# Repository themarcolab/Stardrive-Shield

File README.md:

# STARDRIVE SHIELD

## Introduction
This project has been born because I have been trying to develop an ESC (hardware and firmware) on my own. 
While the most challenging part has been the firmware (being myself a hardware guy), the most frustrating part has been not finding a flexible hardware platform to develop upon.

So I designed one: **STARDRIVE SHIELD**

## Description 
This is a project with the goal of creating a NUCLEO-64 compatible shield to be used as a flexible platform to develop and test ESC firmware, but also for educational purposes. To do so, I included as many features as possible. These features are not mandatory, but they can be implemented (or not) in the firmware (e.g. SPI, I2C, CAN, HALL) or configured through the hardware interface (e.g. overcurrent protection, 6 or 3 PWM). In this way, the STARDRIVE SHIELD grants flexibility to the developer and it is adapt to various needs.

## Features
The **STARDRIVE SHIELD** is built around the [STDRIVE101](https://www.st.com/en/power-management/stdrive101.html)  gate driver and implementing [BSZ099N06LS5](https://www.infineon.com/part/BSZ099N06LS5) MOSFETs.
It presents 3 in-line shunt resistors and 3 relative [INA240A2](https://www.ti.com/lit/ds/symlink/ina240.pdf?ts=1785176124311&ref_url=https%253A%252F%252Fwww.google.com%252F) current sense amplifiers.

With **STARDRIVE SHIELD** you can implement from 6 step to FOC motor control algorithms.

I designed it to be compatible with Nucleo-G474 and Nucleo-F446. Compatibility with other boards has to be verified. 

### Electrical Characteristics
+ Inprut Voltage V<sub>in</sub> = 12 - 48 V
+ Maximum DC current I<sub>dc,max</sub> = 20 A

### Hardware Characteristiscs
+ Three phase gate driver [STDRIVE101](https://www.st.com/en/power-management/stdrive101.html)
  + Configurable 3PWM or 6PWM through the DIP switch
  + Overcurrent protection can be enabled or disabled through the DIP switch.
  + V<sub>ds</sub> protection configurable with resistor divider (disabled by default)
+ [BSZ099N06LS5](https://www.infineon.com/part/BSZ099N06LS5) MOSFETs
+ 3 in-line shunt resistors (1mOhm) with relative 3 INA240A2 Current Sensors
+ JST connectors to implement:
  + I2C (e.g. for magnetic encoder such as [AS5046](https://mm.digikey.com/Volume0/opasdata/d220001/medias/docus/1138/AS5046.pdf))
  + SPI (e.g. for magnetic encoder such as [AS5047P](https://look.ams-osram.com/m/d05ee39221f9857/original/AS5047P-DS000324.pdf))
  + CAN
  + HALL sensors (some BLDC motors have embedded Hall sensors)
  + 3 NTC temperature sensors
+ 10k Potentiometer to use as throttle signal (or whatever you want)
+ 3 GPIO driven LEDs (1 Red, 1 Blue, 1 Green)
+ 1 FAULT LED (RED)
+ CAN RX and TX LEDs
+ Power Good LEDs

## Inspirations
For this project I took inspiration from the [VESC Project](https://vesc-project.com/) and [EVALSTDRIVE101](https://www.st.com/en/evaluation-tools/evalstdrive101.html#cad-resources)

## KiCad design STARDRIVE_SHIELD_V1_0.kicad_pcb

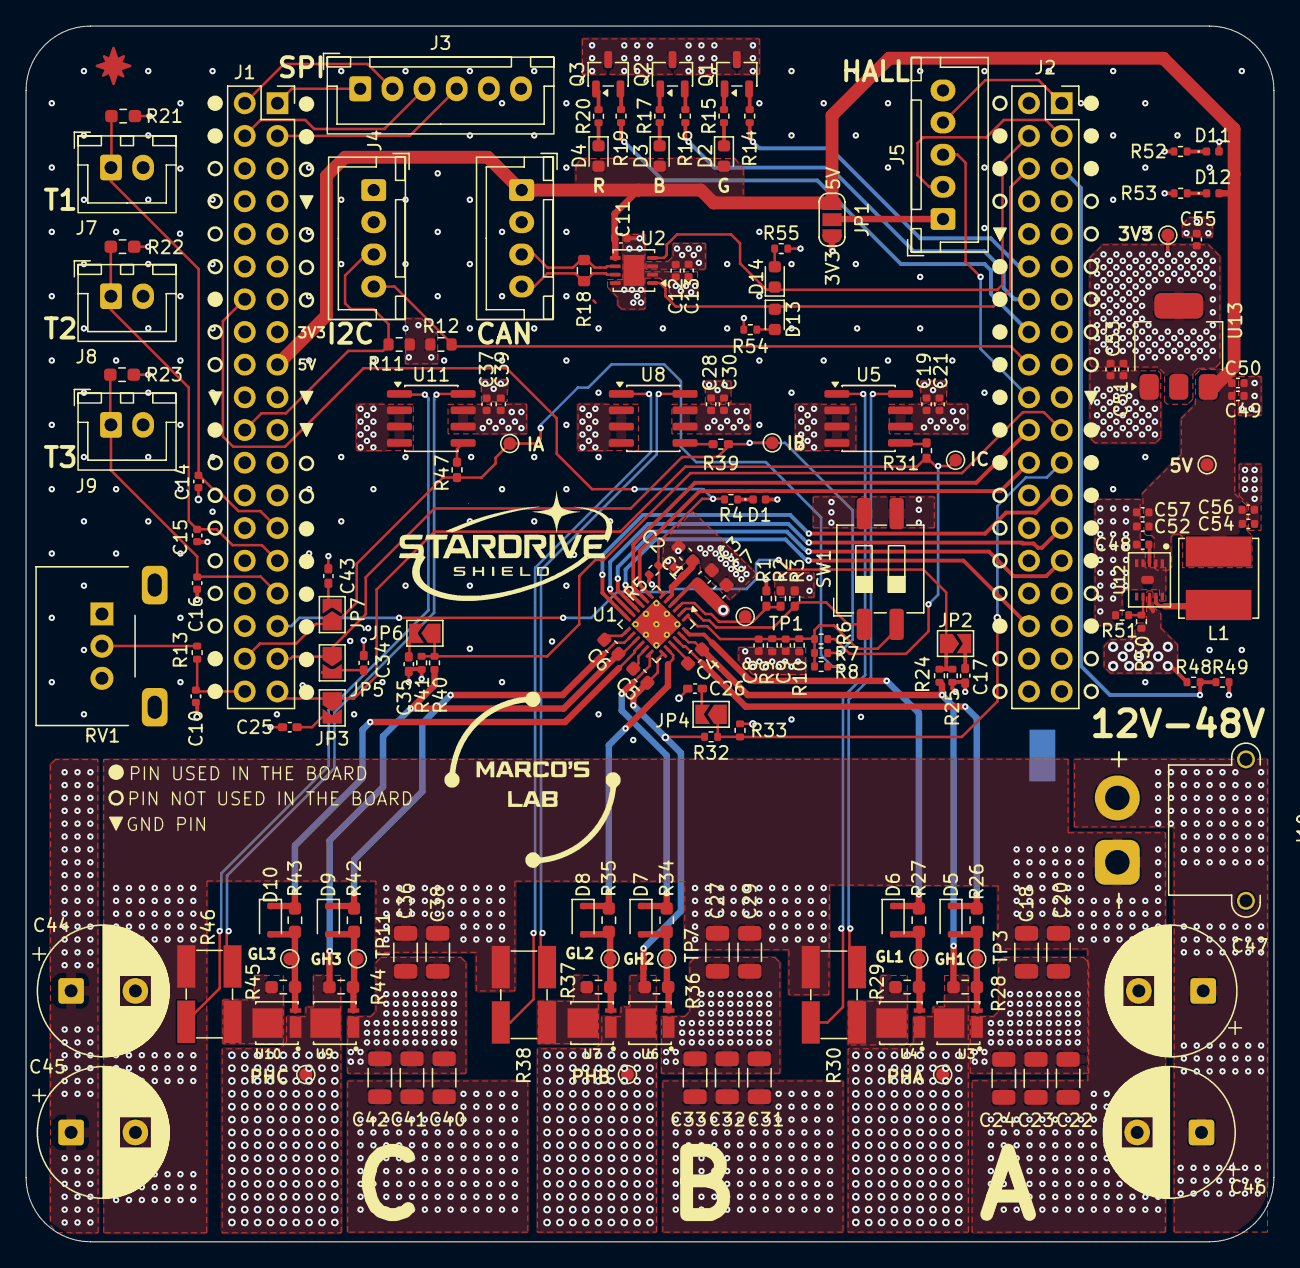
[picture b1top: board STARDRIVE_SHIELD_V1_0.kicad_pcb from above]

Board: 4 copper layers, 97.0 x 94.5 mm, 178 parts (1 on the bottom side), 98 nets.

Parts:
C1: 4u7 25V; C_0603_1608Metric
C2: 100n 25V; C_0402_1005Metric
C3: 100n 100V; C_0603_1608Metric
C4, C5, C6: 1u 25V; C_0603_1608Metric
C7: 1u 100V; C_0603_1608Metric
C8: 3n3 10V; C_0402_1005Metric
C9: NP; C_0402_1005Metric
C10, C13, C21, C30, C39, C50, C51, C52: 100n 10V; C_0402_1005Metric
C11, C12, C14, C15, C16, C19, C28, C37: 2u2 10V; C_0402_1005Metric
C17, C25, C26, C34, C35, C43: 100n 10V; C_0402_1005Metric_Pad0.74x0.62mm_HandSolder
C18, C20, C22, C23, C24, C27, C29, C31, C32, C33, C36, C38, C40, C41, C42: 4u7 100V; C_1206_3216Metric
C44, C45, C46, C47: 220u 63V; CP_Radial_D10.0mm_P5.00mm
C48: 470n 10V; C_0402_1005Metric
C49, C53, C54, C55, C56, C57: 10u 10V; C_0402_1005Metric
D1: RED; LED_0402_1005Metric
D2, D14: GREEN; LED_0603_1608Metric
D3: BLUE; LED_0603_1608Metric
D4, D13: RED; LED_0603_1608Metric
D5, D6, D7, D8, D9, D10: BAT43WS; D_SOD-323F
D11, D12: GREEN; LED_0402_1005Metric
J1, J2: Conn_02x19_Odd_Even; PinSocket_2x19_P2.54mm_Vertical
J3: Conn_01x06_Pin; JST_XH_B6B-XH-A_1x06_P2.50mm_Vertical
J4, J6: Conn_01x04_Pin; JST_XH_B4B-XH-A_1x04_P2.50mm_Vertical
J5: Conn_01x05_Pin; JST_XH_B5B-XH-A_1x05_P2.50mm_Vertical
J7, J8, J9: Conn_01x02_Pin; JST_XH_B2B-XH-A_1x02_P2.50mm_Vertical
J10: XT30PW-M; AMASS_XT30PW-M_1x02_P2.50mm_Horizontal
JP1: SolderJumper_3_Open; SolderJumper-3_P1.3mm_Open_RoundedPad1.0x1.5mm_NumberLabels
JP2, JP3, JP4, JP5, JP6, JP7: SolderJumper; SolderJumper-2_P1.3mm_Open_TrianglePad1.0x1.5mm
L1: 68u; L_Bourns_SRN6045TA
NT1: NetTie_2; NetTie-2_SMD_Pad2.0mm
Q1, Q2, Q3: NMOS; SOT-23-3
R1, R31, R39, R47: 0R; R_0402_1005Metric_Pad0.72x0.64mm_HandSolder
R2: NP; R_0402_1005Metric_Pad0.72x0.64mm_HandSolder
R3: 51k; R_0402_1005Metric_Pad0.72x0.64mm_HandSolder
R4: 470R; R_0402_1005Metric
R5, R6, R7, R8: 10k; R_0402_1005Metric
R9: 1k1; R_0402_1005Metric
R10: NP; R_0402_1005Metric
R11, R12: NP; R_0603_1608Metric
R13, R14, R16, R19: 100R; R_0402_1005Metric
R15, R17, R53, R54, R55: 360R; R_0402_1005Metric
R18: 120R; R_0603_1608Metric
R20: 620R; R_0402_1005Metric
R21, R22, R23, R28, R29, R36, R37, R44, R45: 10k; R_0603_1608Metric_Pad0.98x0.95mm_HandSolder
R24, R32, R40, R48: 56k; R_0402_1005Metric
R25, R33, R41, R49: 3k3; R_0402_1005Metric
R26, R27, R34, R35, R42, R43: 54R9; R_0603_1608Metric_Pad0.98x0.95mm_HandSolder
R30, R38, R46: 1mR; R_Shunt_Ohmite_LVK25
R50: 100k; R_0402_1005Metric
R51: 15k; R_0402_1005Metric
R52: 220R; R_0402_1005Metric
RV1: R_Potentiometer; Potentiometer_Alps_RK09L_Single_Horizontal
SW1: SW_DIP_x02; SW_DIP_SPSTx02_Slide_6.7x6.64mm_W8.61mm_P2.54mm_LowProfile
TP1, TP2, TP3, TP4, TP5, TP6, TP7, TP8, TP9, TP10, TP11, TP12, TP13, TP14, TP15: TestPoint; TestPoint_Pad_D1.0mm
U1: STDRIVE101; QFN-24-1EP_4x4mm_P0.5mm_EP2.8x2.8mm_ThermalVias
U2: TJA1051TK-3; HVSON-8-1EP_3x3mm_P0.65mm_EP1.6x2.4mm
U3, U4, U6, U7, U9, U10: BSZ099N06LS5; PG-TSDSON-8
U5, U8, U11: INA240A2D; SOIC-8_3.9x4.9mm_P1.27mm
U12: L7983; DFN-10-1EP_3mmX3mm_P0.5mm_ExposedPad_0.62x0.98mm
U13: LD1117S33TR; SOT-223-3_TabPin2

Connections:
+3V3: C12.1, C13.1, C19.1, C21.1, C28.1, C30.1, C37.1, C39.1, C51.1, C53.1, C55.1, J1.15, J3.6, J4.1, J7.2, J8.2, J9.2, R11.1, R12.1, RV1.1, U2.3 (VCC), U5.6 (V+), U5.7 (REF1), U8.6 (V+), U8.7 (REF1), U11.6 (V+), U11.7 (REF1), U13.2 (VO)
+5V: C11.1, C49.1, C50.1, C52.1, C54.1, C56.1, C57.1, D2.2 (A), D3.2 (A), D4.2 (A), D12.2 (A), J1.17, J6.1, JP1.3 (B), L1.2, TP15.1 (1_1), U2.5 (VIO), U12.1 (VOUT/FB), U12.2 (VBIAS), U13.3 (VI)
+12V: C1.1, C2.1, U1.5 (REG12)
/Connectors/ADC1.CURR1: J1.37, JP3.1 (A), R6.1, R31.1, TP5.1 (1_1)
/Connectors/ADC1.CURR2: J1.35, JP5.1 (A), R7.1, R39.1, TP9.1 (1_1)
/Connectors/ADC1.CURR3: J1.36, JP7.1 (A), R8.1, R47.1, TP13.1 (1_1)
/Connectors/ADC1.TEMP1: C14.1, J1.27, J7.1, R21.2
/Connectors/ADC1.TEMP2: C15.1, J1.29, J8.1, R22.2
/Connectors/ADC1.TEMP3: C16.1, J1.31, J9.1, R23.2
/Connectors/ADC1.THROTTLE: C10.1, J1.38, R13.1
/Connectors/ADC1.VOLTAGE1: J1.33, JP2.1 (A), R24.2, R25.1
/Connectors/ADC1.VOLTAGE2: J2.23, JP4.1 (A), R32.2, R33.1
/Connectors/ADC1.VOLTAGE3: J2.21, JP6.1 (A), R40.2, R41.1
/Connectors/ADC1.V_BUS: J2.5, R48.2, R49.1
/Connectors/CAN1.CAN+: J6.4, R18.1, U2.7 (CANH)
/Connectors/CAN1.CAN-: J6.3, R18.2, U2.6 (CANL)
/Connectors/CAN1.RX: D14.1 (K), J2.4, U2.4 (RXD)
/Connectors/CAN1.TX: D13.1 (K), J2.6, U2.1 (TXD)
/Connectors/I2C1.SCL: J2.18, J4.4, R12.2
/Connectors/I2C1.SDA: J1.22, J4.3, R11.2
/Connectors/LEDS.BLUE: J2.14, R16.1
/Connectors/LEDS.GREEN: J2.12, R14.1
/Connectors/LEDS.RED: J2.16, R19.1
/Connectors/SPI3.MISO: J1.1, J3.1
/Connectors/SPI3.MOSI: J1.4, J3.3
/Connectors/SPI3.SCK: J1.2, J3.2
/Connectors/SPI3.nCS: J1.3, J3.4
/Connectors/TIM1.PWM1: J2.24, U1.7 (INH1/IN1)
/Connectors/TIM1.PWM2: J2.22, U1.8 (INH2/IN2)
/Connectors/TIM1.PWM3: J2.34, U1.9 (INH3/IN3)
/Connectors/TIM1.PWMN1: J2.29, U1.10 (INL1/EN1)
/Connectors/TIM1.PWMN2: J2.27, U1.11 (INL2/EN2)
/Connectors/TIM1.PWMN3: J2.25, U1.12 (INL3/EN3)
/Connectors/TIM3.HALL1: J2.3, J5.2
/Connectors/TIM3.HALL2: J2.20, J5.3
/Connectors/TIM3.HALL3: J2.1, J5.4
/Connectors/nFAULT: J1.14, R4.2, R5.2, U1.6 (nFAULT)
/Interfaces/+V_HALL: J5.1, JP1.2 (C)
/Inverter/CP: C8.1, C9.1, R6.2, R7.2, R8.2, R9.2, R10.2, SW1.2, U1.1 (CP)
/Inverter/DT/MODE: R3.1, SW1.1, U1.2 (DT/MODE)
/Inverter/Half-Bridge1/GH: D5.1, R26.1, U1.22 (GHS1)
/Inverter/Half-Bridge1/GL: D6.1, R27.1, U1.24 (GLS1)
/Inverter/Half-Bridge1/PH: C4.2, R24.1, R28.1, TP2.1 (1_1), U1.23 (OUT1), U3.3, U4.1
/Inverter/Half-Bridge1/R_SNS+: R30.2, U5.8 (+)
/Inverter/Half-Bridge1/R_SNS-: R30.3, U5.1 (-)
/Inverter/Half-Bridge2/GH: D7.1, R34.1, U1.18 (GHS2)
/Inverter/Half-Bridge2/GL: D8.1, R35.1, U1.20 (GLS2)
/Inverter/Half-Bridge2/PH: C5.2, R32.1, R36.1, TP6.1 (1_1), U1.19 (OUT2), U6.3, U7.1
/Inverter/Half-Bridge2/R_SNS+: R38.2, U8.8 (+)
/Inverter/Half-Bridge2/R_SNS-: R38.3, U8.1 (-)
/Inverter/Half-Bridge3/GH: D9.1, R42.1, U1.14 (GHS3)
/Inverter/Half-Bridge3/GL: D10.1, R43.1, U1.16 (GLS3)
/Inverter/Half-Bridge3/PH: C6.2, R40.1, R44.1, TP10.1 (1_1), U1.15 (OUT3), U9.3, U10.1
/Inverter/Half-Bridge3/R_SNS+: R46.2, U11.8 (+)
/Inverter/Half-Bridge3/R_SNS-: R46.3, U11.1 (-)
/Inverter/SCREF: R1.2, R2.1, TP1.1 (1_1), U1.3 (SCREF)
GND: C1.2, C2.2, C3.2, C7.2, C8.2, C9.2, C10.2, C11.2, C12.2, C13.2, C14.2, C15.2, C16.2, C17.2, C19.2, C21.2, C25.2, C26.2, C28.2, C30.2, C34.2, C35.2, C37.2, C39.2, C43.2, C48.2, C49.2, C50.2, C51.2, C52.2, C53.2, C54.2, C55.2, C56.2, C57.2, D1.2 (A), D11.2 (A), J1.7, J1.19, J1.20, J1.21, J2.10, J2.19, J3.5, J4.2, J5.5, J6.2, JP1.1 (A), NT1.1, Q1.3 (S), Q2.3 (S), Q3.3 (S), R1.1, R2.2, R3.2, R5.1, R9.1, R10.1, R21.1, R22.1, R23.1, R25.2, R33.2, R41.2, R49.2, R51.2, R52.2, R53.2, R54.1, R55.1, RV1.3, RV1.MP (MountPin), SW1.3, SW1.4, TP14.1 (1_1), U1.25 (GND/EPAD), U2.2 (GND), U2.8 (S), U2.9 (GND), U5.2 (GND), U5.3 (REF2), U5.4 (GND), U8.2 (GND), U8.3 (REF2), U8.4 (GND), U11.2 (GND), U11.3 (REF2), U11.4 (GND), U12.4 (FSW), U12.5 (LNM/nLCM), U12.10 (GND), U12.11 (EPAD), U13.1 (GND)
unnamed: D1.1 (K), R4.1
unnamed: D2.1 (K), R15.1
unnamed: D3.1 (K), R17.1
unnamed: D4.1 (K), R20.1
unnamed: D5.2, R26.2, R28.2, TP3.1 (1_1), U3.2
unnamed: D6.2, R27.2, R29.2, TP4.1 (1_1), U4.2
unnamed: D7.2, R34.2, R36.2, TP7.1 (1_1), U6.2
unnamed: D8.2, R35.2, R37.2, TP8.1 (1_1), U7.2
unnamed: D9.2, R42.2, R44.2, TP11.1 (1_1), U9.2
unnamed: D10.2, R43.2, R45.2, TP12.1 (1_1), U10.2
unnamed: D11.1 (K), R52.1
unnamed: D12.1 (K), R53.1
unnamed: D13.2 (A), R54.2
unnamed: D14.2 (A), R55.2
unnamed: C17.1, JP2.2 (B)
unnamed: C25.1, JP3.2 (B)
unnamed: C26.1, JP4.2 (B)
unnamed: C34.1, JP5.2 (B)
unnamed: C35.1, JP6.2 (B)
unnamed: C43.1, JP7.2 (B)
unnamed: Q1.1 (D), R15.2
unnamed: Q1.2 (G), R14.2
unnamed: Q2.1 (D), R17.2
unnamed: Q2.2 (G), R16.2
unnamed: Q3.1 (D), R20.2
unnamed: Q3.2 (G), R19.2
unnamed: R13.2, RV1.2
unnamed: R29.1, R30.1, U4.3
unnamed: R31.2, U5.5
unnamed: R37.1, R38.1, U7.3
unnamed: R39.2, U8.5
unnamed: R45.1, R46.1, U10.3
unnamed: R47.2, U11.5
unnamed: C4.1, U1.21 (BOOT1)
unnamed: C5.1, U1.17 (BOOT2)
unnamed: C6.1, U1.13 (BOOT3)
unnamed: R50.2, R51.1, U12.7 (EN/UVLO)
unnamed: L1.1, U12.9 (LX)
unnamed: C48.1, U12.3 (VCC)
PGND: C18.2, C20.2, C22.2, C23.2, C24.2, C27.2, C29.2, C31.2, C32.2, C33.2, C36.2, C38.2, C40.2, C41.2, C42.2, C44.2, C45.2, C46.2, C47.2, J10.1, NT1.2, R30.4, R38.4, R46.4
VBUS: C3.1, C7.1, C18.1, C20.1, C22.1, C23.1, C24.1, C27.1, C29.1, C31.1, C32.1, C33.1, C36.1, C38.1, C40.1, C41.1, C42.1, C44.1, C45.1, C46.1, C47.1, J10.2, R48.1, R50.1, U1.4 (VS), U3.1, U6.1, U9.1, U12.8 (VIN)
